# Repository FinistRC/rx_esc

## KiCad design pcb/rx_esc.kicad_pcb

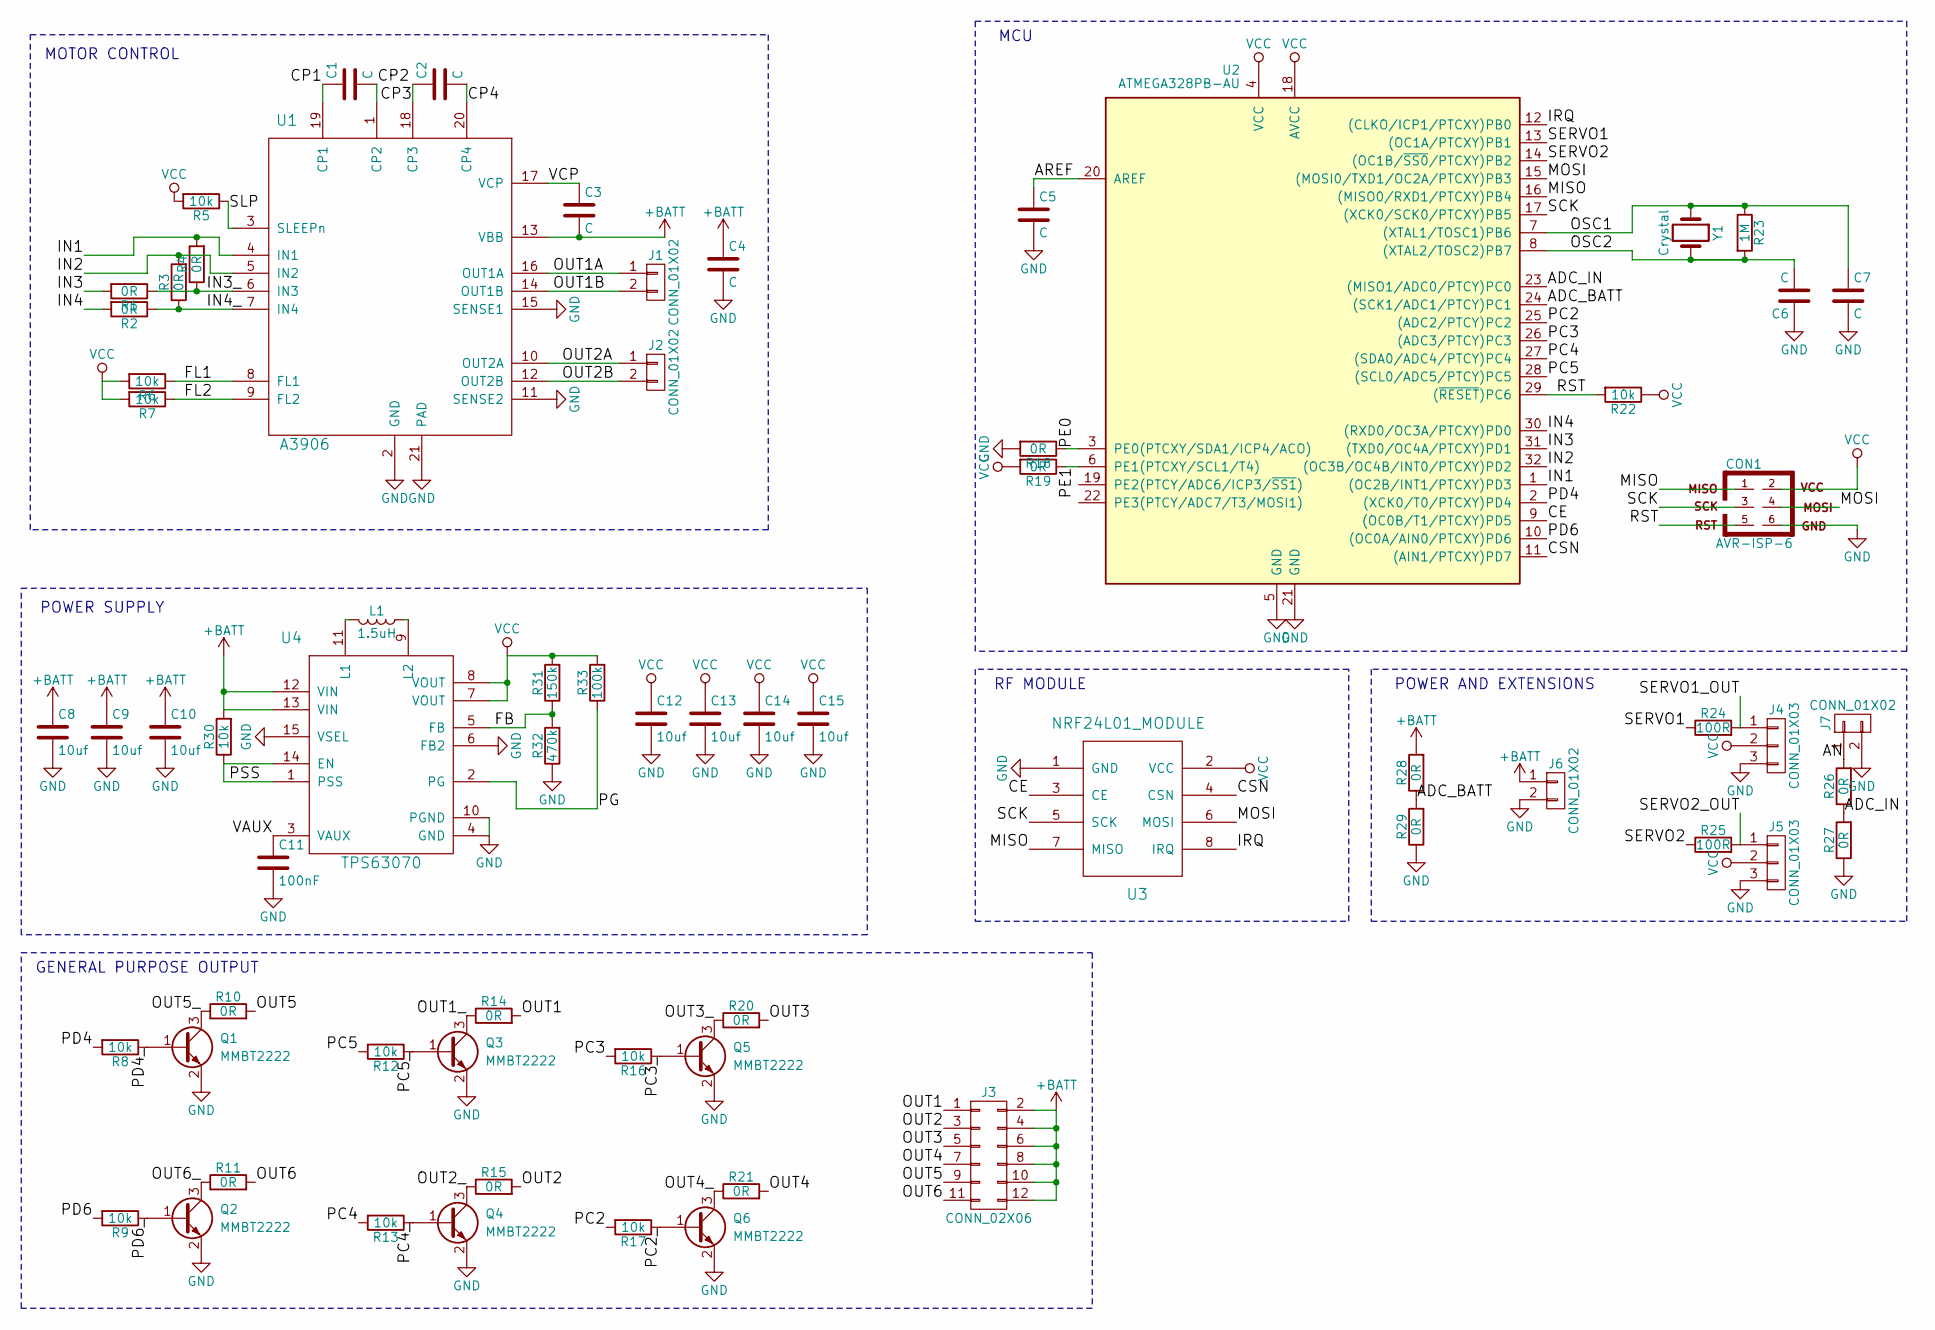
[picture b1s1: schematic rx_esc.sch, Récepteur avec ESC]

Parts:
C1, C2, C4: C; C_0603
C3, C5, C6, C7: C; C_0402
C8, C12: 10uf; C_0603
C9, C10, C13, C14, C15: 10uf; C_0805
C11: 100nF; C_0402
CON1: AVR-ISP-6; Pin_Header_Straight_2x03
J1, J2, J6, J7: CONN_01X02; Pin_Header_Straight_1x02
J3: CONN_02X06; Pin_Header_Straight_2x06
J4, J5: CONN_01X03; Pin_Header_Straight_1x03
L1: 1.5uH; L_Coilcraft_XAL5030
Q1, Q2, Q3, Q4, Q5, Q6: MMBT2222; SC-70
R1, R2, R3, R4: 0R; R_0603
R5, R6, R7, R8, R9, R12, R13, R16, R17, R22, R30: 10k; R_0402
R10, R11, R14, R15, R18, R19, R20, R21, R26, R27, R28, R29: 0R; R_0402
R23: 1M; R_0402
R24, R25: 100R; R_0402
R31: 150k; R_0402
R32: 470k; R_0402
R33: 100k; R_0402
U1: A3906; QFN-20-1EP_4x4mm_Pitch0.5mm
U2: ATMEGA328PB-AU; TQFP-32_7x7mm_Pitch0.8mm
U3: NRF24L01_MODULE; nRF24L01_Breakout
U4: TPS63070; QFN-16-1EP_3x3mm_Pitch0.5mm
Y1: Crystal; crystal_FA238-TSX3225

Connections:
+BATT: C3.2, C4.1, C8.1, C9.1, C10.1, J3.2, J3.4, J3.6, J3.8, J3.10, J3.12, J6.1, R28.2, R30.2, U1.13 (VBB), U4.12 (VIN), U4.13 (VIN)
/ADC_BATT: R28.1, R29.2, U2.24 ((SCK1/ADC1/PTCY)PC1)
/ADC_IN: R26.1, R27.2, U2.23 ((MISO1/ADC0/PTCY)PC0)
/AN: J7.1, R26.2
/AREF: C5.1, U2.20 (AREF)
/CE: U2.9 ((OC0B/T1/PTCXY)PD5), U3.3 (CE)
/CP1: C1.1, U1.19 (CP1)
/CP2: C1.2, U1.1 (CP2)
/CP3: C2.1, U1.18 (CP3)
/CP4: C2.2, U1.20 (CP4)
/CSN: U2.11 ((AIN1/PTCXY)PD7), U3.4 (CSN)
/FB: R31.1, R32.2, U4.5 (FB)
/FL1: R6.1, U1.8 (FL1)
/FL2: R7.1, U1.9 (FL2)
/IN1: R4.2, U1.4 (IN1), U2.1 ((OC2B/INT1/PTCXY)PD3)
/IN2: R3.2, U1.5 (IN2), U2.32 ((OC3B/OC4B/INT0/PTCXY)PD2)
/IN3: R1.2, U2.31 ((TXD0/OC4A/PTCXY)PD1)
/IN3_: R1.1, R4.1, U1.6 (IN3)
/IN4: R2.2, U2.30 ((RXD0/OC3A/PTCXY)PD0)
/IN4_: R2.1, R3.1, U1.7 (IN4)
/IRQ: U2.12 ((CLKO/ICP1/PTCXY)PB0), U3.8 (IRQ)
/MISO: CON1.1, U2.16 ((MISO0/RXD1/PTCXY)PB4), U3.7 (MISO)
/MOSI: CON1.4, U2.15 ((MOSI0/TXD1/OC2A/PTCXY)PB3), U3.6 (MOSI)
/OSC1: C7.1, R23.1, U2.7 ((XTAL1/TOSC1)PB6), Y1.1
/OSC2: C6.2, R23.2, U2.8 ((XTAL2/TOSC2)PB7), Y1.2
/OUT1: J3.1, R14.2
/OUT1A: J1.1, U1.16 (OUT1A)
/OUT1B: J1.2, U1.14 (OUT1B)
/OUT1_: Q3.3 (C), R14.1
/OUT2: J3.3, R15.2
/OUT2A: J2.1, U1.10 (OUT2A)
/OUT2B: J2.2, U1.12 (OUT2B)
/OUT2_: Q4.3 (C), R15.1
/OUT3: J3.5, R20.2
/OUT3_: Q5.3 (C), R20.1
/OUT4: J3.7, R21.2
/OUT4_: Q6.3 (C), R21.1
/OUT5: J3.9, R10.2
/OUT5_: Q1.3 (C), R10.1
/OUT6: J3.11, R11.2
/OUT6_: Q2.3 (C), R11.1
/PC2: R17.2, U2.25 ((ADC2/PTCY)PC2)
/PC2_: Q6.1 (B), R17.1
/PC3: R16.2, U2.26 ((ADC3/PTCY)PC3)
/PC3_: Q5.1 (B), R16.1
/PC4: R13.2, U2.27 ((SDA0/ADC4/PTCY)PC4)
/PC4_: Q4.1 (B), R13.1
/PC5: R12.2, U2.28 ((SCL0/ADC5/PTCY)PC5)
/PC5_: Q3.1 (B), R12.1
/PD4: R8.2, U2.2 ((XCK0/T0/PTCXY)PD4)
/PD4_: Q1.1 (B), R8.1
/PD6: R9.2, U2.10 ((OC0A/AIN0/PTCXY)PD6)
/PD6_: Q2.1 (B), R9.1
/PE0: R18.1, U2.3 (PE0(PTCXY/SDA1/ICP4/ACO))
/PE1: R19.1, U2.6 (PE1(PTCXY/SCL1/T4))
/PG: R33.1, U4.2 (PG)
/PSS: R30.1, U4.1 (PSS), U4.14 (EN)
/RST: CON1.5, R22.2, U2.29 ((~RESET~)PC6)
/SCK: CON1.3, U2.17 ((XCK0/SCK0/PTCXY)PB5), U3.5 (SCK)
/SERVO1: R24.1, U2.13 ((OC1A/PTCXY)PB1)
/SERVO1_OUT: J4.1, R24.2
/SERVO2: R25.1, U2.14 ((OC1B/~SS0~/PTCXY)PB2)
/SERVO2_OUT: J5.1, R25.2
/SLP: R5.1, U1.3 (SLEEPn)
/VAUX: C11.1, U4.3 (VAUX)
/VCP: C3.1, U1.17 (VCP)
GND: C4.2, C5.2, C6.1, C7.2, C8.2, C9.2, C10.2, C11.2, C12.2, C13.2, C14.2, C15.2, CON1.6, J4.3, J5.3, J6.2, J7.2, Q1.2 (E), Q2.2 (E), Q3.2 (E), Q4.2 (E), Q5.2 (E), Q6.2 (E), R18.2, R27.1, R29.1, R32.1, U1.2 (GND), U1.11 (SENSE2), U1.15 (SENSE1), U1.21 (PAD), U2.5 (GND), U2.21 (GND), U3.1 (GND), U4.4 (GND), U4.6 (FB2), U4.10 (PGND), U4.15 (VSEL)
unnamed: L1.1, U4.9 (L2)
unnamed: L1.2, U4.11 (L1)
VCC: C12.1, C13.1, C14.1, C15.1, CON1.2, J4.2, J5.2, R5.2, R6.2, R7.2, R19.2, R22.1, R31.2, R33.2, U2.4 (VCC), U2.18 (AVCC), U3.2 (VCC), U4.7 (VOUT), U4.8 (VOUT)

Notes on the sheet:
POWER AND EXTENSIONS
RF MODULE
MCU
MOTOR CONTROL
POWER SUPPLY
GENERAL PURPOSE OUTPUT

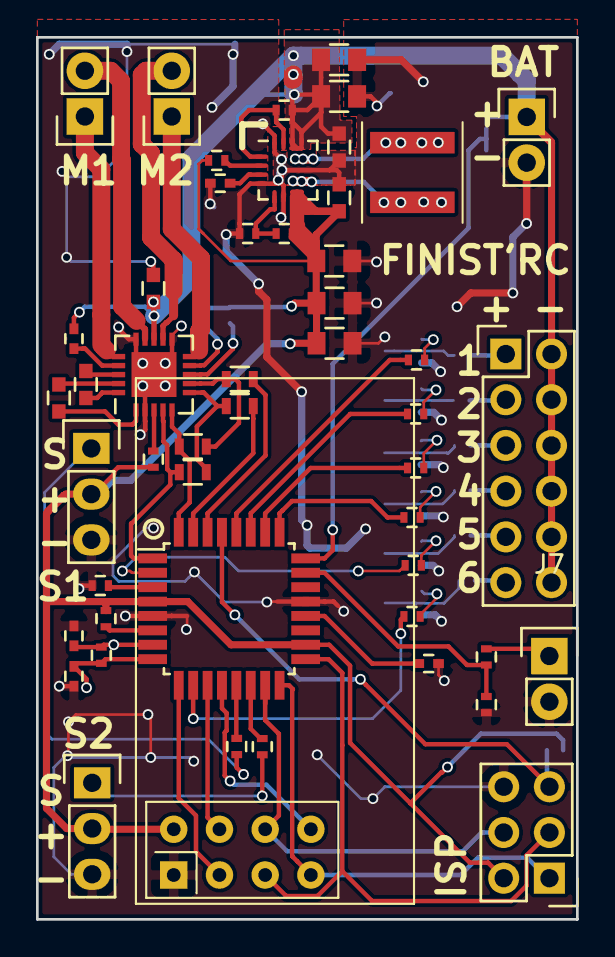
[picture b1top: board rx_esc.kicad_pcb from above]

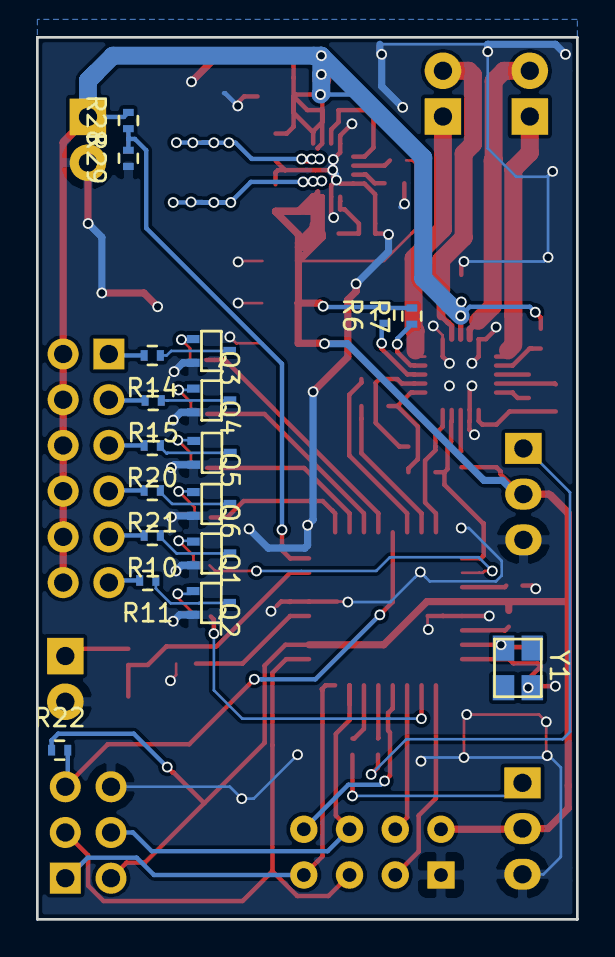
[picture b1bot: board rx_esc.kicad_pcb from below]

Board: 2 copper layers, 30.0 x 49.0 mm, 68 parts (18 on the bottom side), 70 nets.

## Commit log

2017-12-02 VE 02-12-17 PCB first schema, component placement Todo: add the power IC
2017-12-24 VE 24-12-17 Add power supply
2017-12-24 VE 24-12-2017 update schematic pdf
2017-12-25 VE 25-12-17 PCB routed schematic updated
2017-12-25 VE 25-12-17 Panelized pcb add fab directory generate fab files
